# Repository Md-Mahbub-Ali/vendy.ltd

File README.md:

# vendy.ltd
# To print a new PCB - JUST DOWNLOAD the "VENDYVERSION2.999.pdf " file and print it. 
# Important Eagle Libraries have been included 
# All the files related to design a PCB have been included

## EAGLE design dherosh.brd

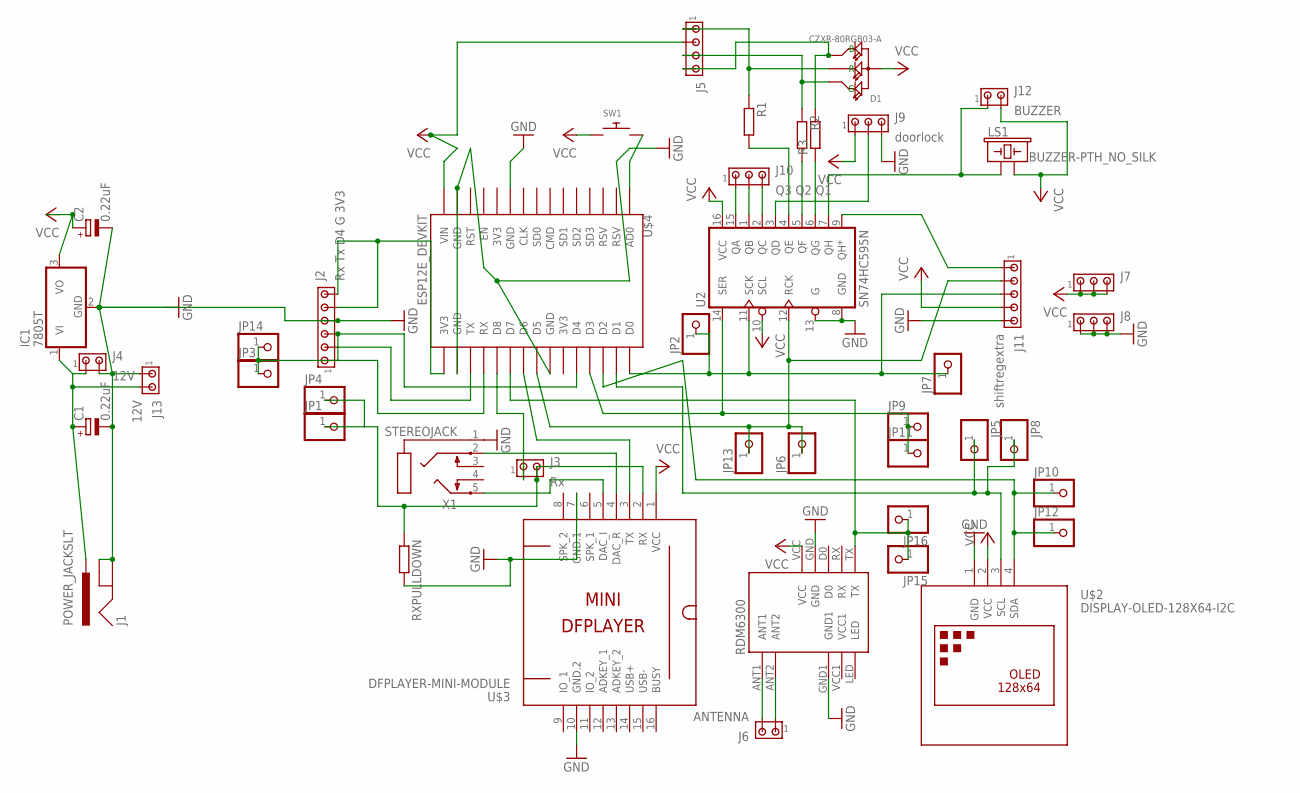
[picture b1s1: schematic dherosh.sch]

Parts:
C1, C2: 0.22uF; E2-5
D1: CZXR-80RGB03-A; LED4-2.0-D8.0MM
IC1: 7805T; TO220H
J1: POWER_JACKSLT; POWER_JACK_SLOT
J2: Rx Tx D4 G 3V3; 10X06MTA
J3: Rx; 10X02MTA
J4, J13: 12V; 10X02MTA
J5: MTA04-100; 10X04MTA
J6: ANTENNA; 10X02MTA
J7, J8: MTA03-100; 10X03MTA
J9: doorlock; 10X03MTA
J10: Q3 Q2 Q1; 10X03MTA
J11: shiftregextra; 10X05MTA
J12: BUZZER; 10X02MTA
JP1, JP2, JP3, JP4, JP5, JP6, JP7, JP8, JP9, JP10, JP11, JP12, JP13, JP14, JP15, JP16: PINHD-1X1; 1X01
LS1: BUZZER-PTH_NO_SILK; BUZZER-12MM-NS
R1, R2, R3: R-EU_0204/7; 0204/7
RDM1: RDM6300
RXPULLDOWN: R-EU_0204/7; 0204/7
SW1: SWITCH_PUSHBUTTONEVQ-PE; TACT_PANA-EVQ
U2: SN74HC595N; DIP16
U$2: DISPLAY-OLED-128X64-I2C
U$3: DFPLAYER-MINI-MODULE
U$4: ESP12E_DEVKIT
X1: STEREOJACK; STX3100

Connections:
GND: C1.-, C2.-, IC1.2 (GND), J1.GND@1 (GNDBREAK), J1.GND@2 (GND), J2.4, J4.2, J8.1, J8.2, J8.3, J9.3, J11.5, J13.1, RDM1.GND, RDM1.GND1, RXPULLDOWN.2, U2.8 (GND), U2.13 (G), U$2.1 (GND), U$3.7 (GND.1), U$3.10 (GND.2), U$4.GND@0 (GND), U$4.GND@1 (GND), U$4.GND@2 (GND), U$4.GND@3 (GND), X1.1
unnamed: C1.+, IC1.1 (VI), J1.PWR, J4.1, J13.2
unnamed: J2.5, J2.6, U$4.3V3@2 (3V3)
unnamed: U$3.3 (TX), U$4.D6
unnamed: J2.3, JP3.1, JP14.1, U$4.D4
unnamed: U$3.5 (DAC_I), X1.5
unnamed: U$3.4 (DAC_R), X1.2
unnamed: J11.3, JP2.1, JP7.1, U2.11 (SCK), U$4.D0
unnamed: J11.2, JP6.1, JP13.1, U2.12 (RCK), U$4.D5
unnamed: J3.2, JP1.1, JP4.1, RXPULLDOWN.1, U$3.2 (RX)
unnamed: JP15.1, JP16.1, RDM1.TX, U$4.D7
unnamed: JP5.1, JP8.1, U$2.3 (SCL), U$4.D1
unnamed: JP10.1, JP12.1, U$2.4 (SDA), U$4.D2
unnamed: J10.1, U2.15 (QA)
unnamed: D1.4 (B), J5.4, R3.2
unnamed: R3.1, U2.6 (QG)
unnamed: D1.1 (R), J5.1, R1.1
unnamed: R2.2, U2.5 (QF)
unnamed: SW1.P$2, U$4.AD0
unnamed: J11.1, U2.9 (QH*)
unnamed: J12.1, LS1.+ (1), U2.7 (QH)
unnamed: J10.2, U2.1 (QB)
unnamed: J10.3, U2.2 (QC)
unnamed: J2.1, U$4.RX
unnamed: J9.2, U2.3 (QD)
unnamed: R1.2, U2.4 (QE)
unnamed: J2.2, U$4.TX
unnamed: J6.2, RDM1.ANT1
unnamed: J6.1, RDM1.ANT2
unnamed: J3.1, U$4.D8
unnamed: JP9.1, JP11.1, U2.14 (SER), U$4.D3
unnamed: D1.3 (G), J5.3, R2.1
VCC: C2.+, D1.2 (+), IC1.3 (VO), J5.2, J7.1, J7.2, J7.3, J9.1, J11.4, J12.2, LS1.- (2), RDM1.VCC, SW1.P$1, U2.10 (SCL), U2.16 (VCC), U$2.2 (VCC), U$3.1 (VCC), U$4.VIN

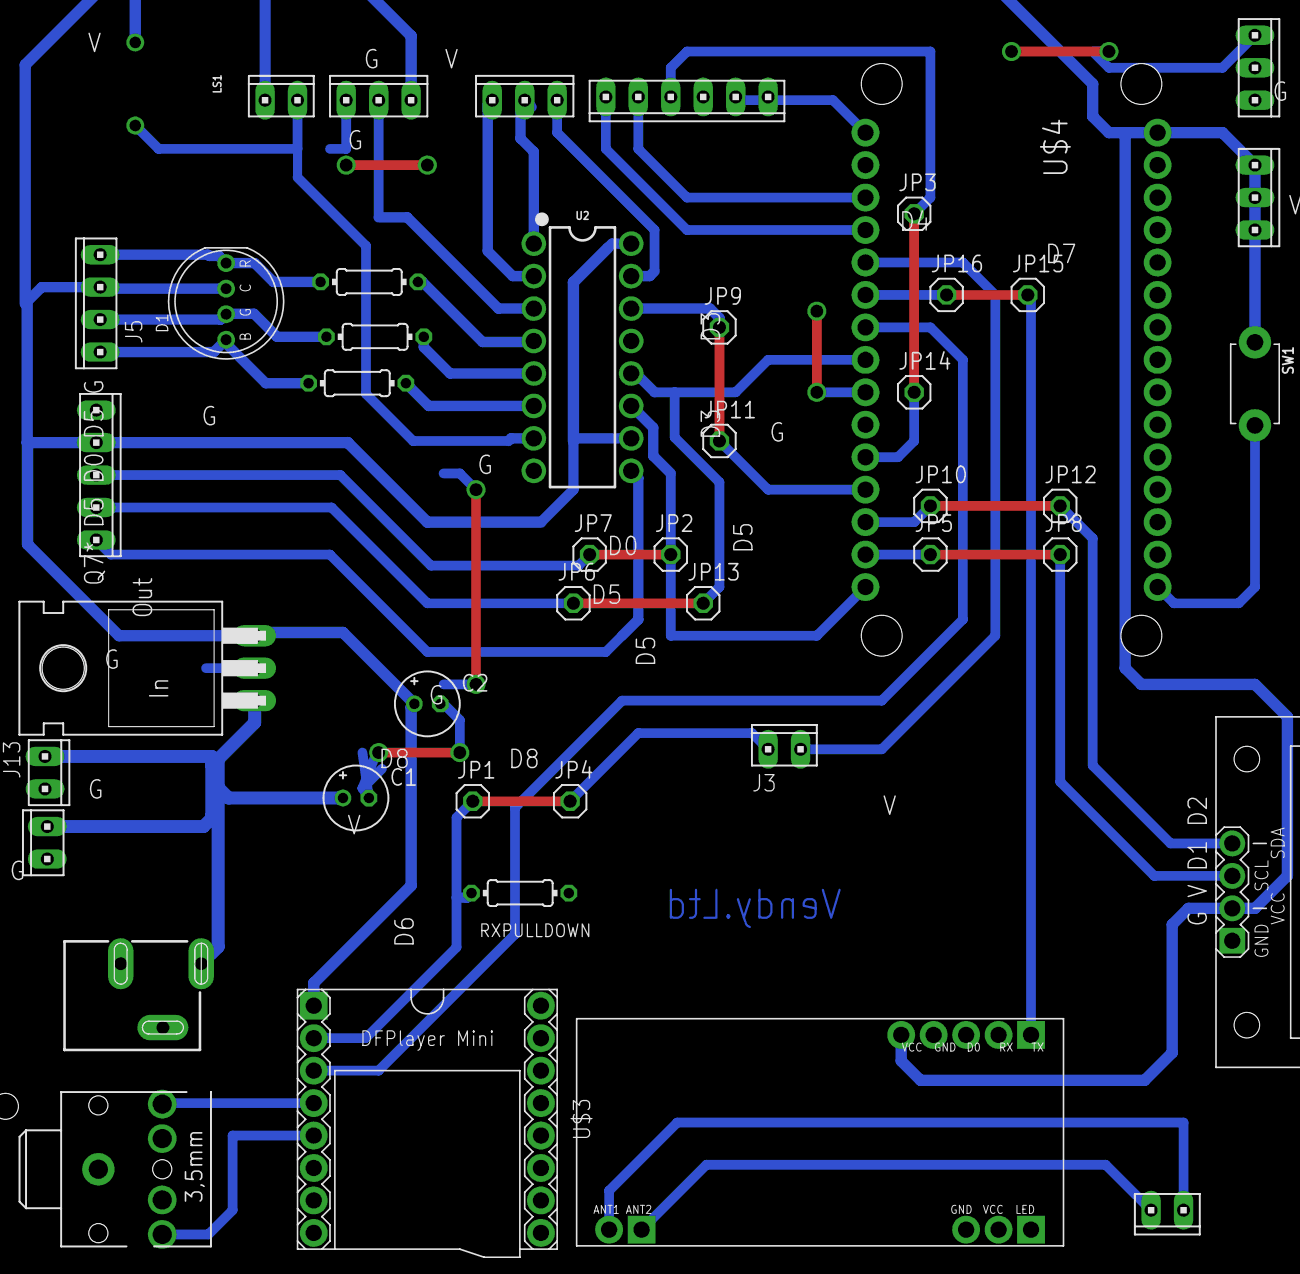
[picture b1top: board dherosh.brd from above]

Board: 2 copper layers, 45 parts (0 on the bottom side), 33 nets.

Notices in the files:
parts and their libraries:
SparkFun-Connectors: Licensing: Creative Commons ShareAlike 4.0 International - https://creativecommons.org/licenses/by-sa/4.0
diy-modules: Released under the Creative Commons Attribution 4.0 International License: http://creativecommons.org/licenses/by/4.0
